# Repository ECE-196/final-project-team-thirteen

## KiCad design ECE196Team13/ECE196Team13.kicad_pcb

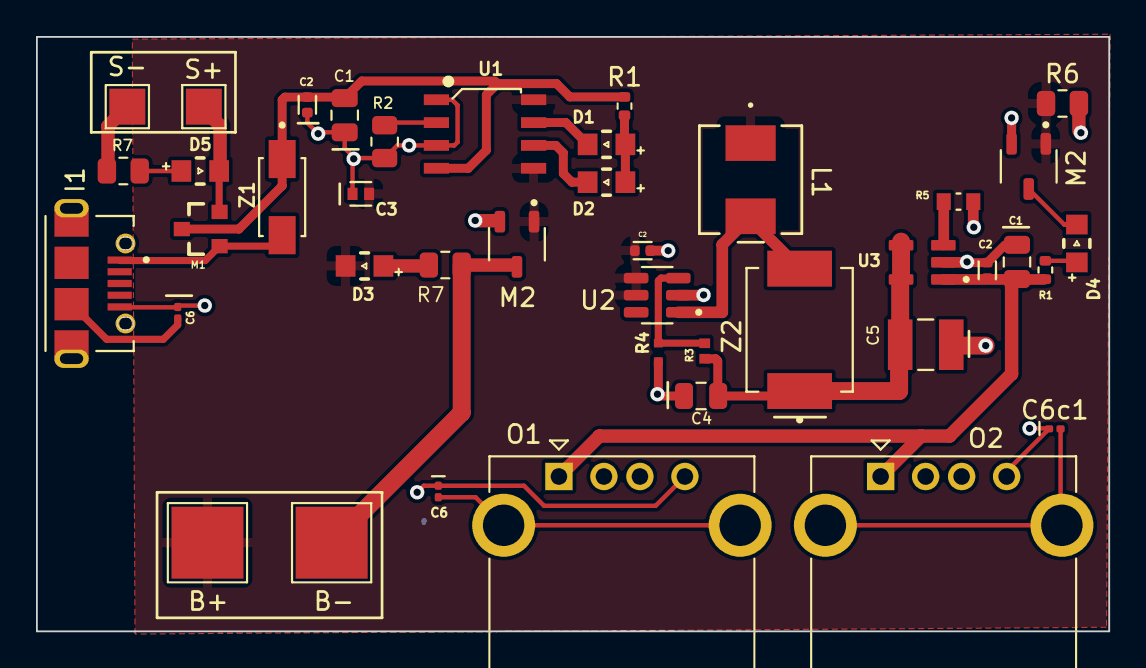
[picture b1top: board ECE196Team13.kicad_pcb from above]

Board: 2 copper layers, 59.6 x 33.0 mm, 41 parts (0 on the bottom side), 22 nets.

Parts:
B+: TestPoint; TestPoint_Pad_4.0x4.0mm
B-: TestPoint; TestPoint_Pad_4.0x4.0mm
C1, C1#2: 10uF; C_0805_2012Metric
C2, C2#2, C2#3: 100nF; CAPC1005X55N
C3: 4.7uF; CAPC1005X65N
C4: 1uF; C_0805_2012Metric
C5: 47uF, 25V; CAPC3225X280N
C6, C6#2, C6c1: 1nF; C_0201_0603Metric
D1: CHRG; WL-SMCW_0805
D2: DONE; WL-SMCW_0805
D3: BATT; WL-SMCW_0805
D4: On/Off; WL-SMCW_0805
D5: SOLAR; WL-SMCW_0805
I1: USB_Micro_AB; MOLEX_47589-0001
L1: 4.7uH; IND_IHLP-2020BZ_VIS
M1: AO3401A; SOT23-3
M2, M2#2: AO3400A; SOT95P280X125-3N
O1, O2: USB_A; USB_A_CONNFLY_DS1095-WNR0
R1, R1#2: 10k; R_0402_1005Metric
R2: 2k; R_0805_2012Metric
R3: 150k; RESC1005X40N
R4: 20k; RES_ERJ2RKF2002X
R5: 6.8k; RESC1608X55N
R6: 1M; R_0805_2012Metric
R7, R7#2: 1K; R_0805_2012Metric
S+: TestPoint; TestPoint_Pad_2.0x2.0mm
S-: TestPoint; TestPoint_Pad_2.0x2.0mm
U1: CN3063-SOIC8; SOIC8-1.27-5X4MM
U2: MT3608; SOT95P280X145-6N
U3: SY6280AAC; SOT95P285X130-5N
Z1: SK34A; DIOM4325X250N
Z2: SS34; DIO_SS34

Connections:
+6V: D5.1 (K), M1.2, S+.1
+BATT: B+.1, C2#2.1, C3.1, D3.1 (K), L1.1, M2.1, M2#2.1, R6.1, U1.5 (BAT), U1.8 (FB), U2.4 (EN), U2.5 (IN)
-BATT: B-.1, M2.3, R7#2.1
GND: C1.2, C1#2.2, C2.2, C2#2.2, C2#3.2, C3.2, C4.2, C5.2, C6.2, C6#2.2, C6c1.1, I1.5 (GND), M2.2, M2#2.2, O1.4 (GND), O2.4 (GND), R2.2, R4.2, R5.2, R6.2, U1.1 (TEMP), U1.3 (GND), U2.2 (GND), U3.2 (GND)
unnamed: I1.1 (VBUS), M1.1, Z1.A
unnamed: D1.2 (A), D2.2 (A), R1#2.2
unnamed: D1.1 (K), U1.7 (~CHRG)
unnamed: D2.1 (K), U1.6 (~DONE)
unnamed: D3.2 (A), R7#2.2
unnamed: D4.2 (A), R1.2
unnamed: D4.1 (K), M2#2.3
unnamed: D5.2 (A), R7.2
unnamed: C6.1, O1.5 (Shield)
unnamed: C1.1, C2#3.1, O1.1 (VBUS), O2.1 (VBUS), R1.1, U3.1 (OUT)
unnamed: C6c1.2, O2.5 (Shield)
unnamed: R7.1, S-.1
unnamed: R2.1, U1.2 (ISET)
unnamed: C1#2.1, C2.1, M1.3, R1#2.1, U1.4 (VIN), Z1.C
unnamed: R3.2, R4.1, U2.3 (FB)
unnamed: L1.2, U2.1 (SW), Z2.A
unnamed: C4.1, C5.1, R3.1, U3.4 (EN), U3.5 (IN), Z2.C
unnamed: R5.1, U3.3 (ISET)

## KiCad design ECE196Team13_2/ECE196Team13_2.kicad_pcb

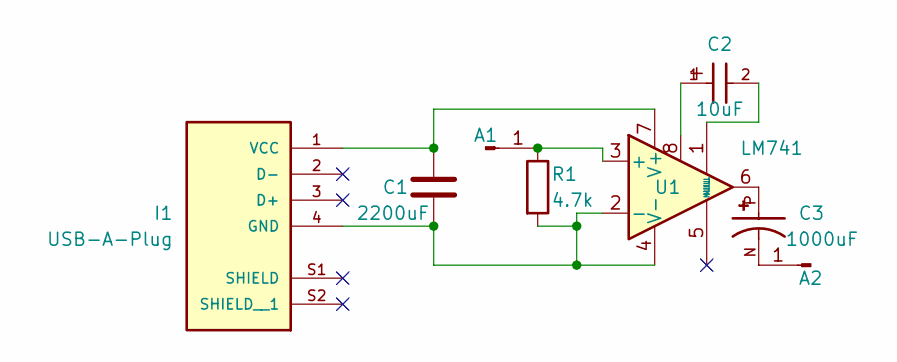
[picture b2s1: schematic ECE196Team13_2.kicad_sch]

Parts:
A1, A2: Conn_01x01_Pin; Pin_D0.7mm_L6.5mm_W1.8mm_FlatFork
C1: 2200uF; CP_Radial_D5.0mm_P2.00mm
C2: 10uF; WCAP-ATG8_5X11_DXL_; DigiKey_Part_Number 732-8593-1-ND
C3: 1000uF; CAPPRD350W60D800H1150; PARTREV 20-DEC-19
I1: USB-A-Plug; MOLEX_48037-0001; PARTREV D
R1: 4.7k; R_Axial_DIN0204_L3.6mm_D1.6mm_P5.08mm_Vertical
U1: LM741; DIP794W45P254L959H508Q8

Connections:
unnamed: A1.1, R1.1, U1.3 (+)
unnamed: A2.1, C3.N
unnamed: C2.1, U1.8
unnamed: C2.2, U1.1 (NULL)
unnamed: C3.P, U1.6
unnamed: C1.2, I1.4 (GND), R1.2, U1.2 (-), U1.4 (V-)
unnamed: C1.1, I1.1 (VCC), U1.7 (V+)

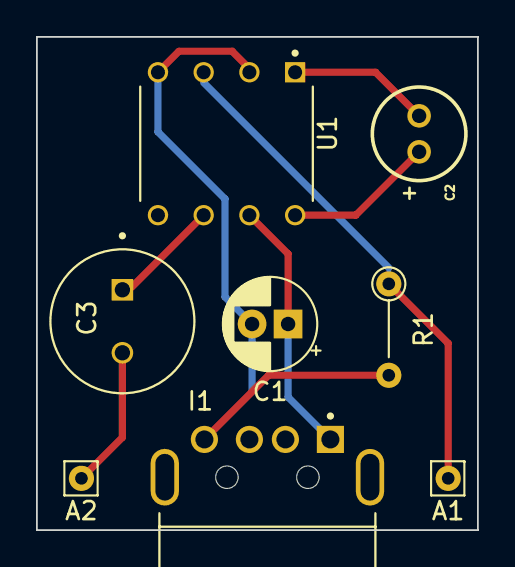
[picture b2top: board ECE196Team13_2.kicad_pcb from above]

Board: 2 copper layers, 24.5 x 27.4 mm, 8 parts (0 on the bottom side), 7 nets.

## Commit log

2024-10-21 Some references
    references
2024-10-31 Team13GerbersSolarBattery
    This is the set of gerbers for our main PCB. All SMD components.
2024-10-31 Team13GerbersAmplifier
    This is the set of our gerbers for the amplifier. All through hole. No copper pour because so few components.
2024-10-31 Schematics for both of our circuits.
2024-10-31 Team13KicadFileSolarBattery
    Includes everything.
2024-10-31 Team13KicadAmplifier
    Everything for amplifier. Downloaded footprints and designs in the imports folder.
2024-10-31 Fixed Gerbers oops
2024-10-31 Also fixed. We forgot one connection.
2024-10-31 Updates to Solar Battery Stuff
    New gerbers, new schematic kind-of (going to make it prettier later), new pcb design. MT3608 and Sy6280AAC layouts should be better.
2024-12-01 Added a bunch of photos
    Got the photos of the actual project and our poster and just some others
